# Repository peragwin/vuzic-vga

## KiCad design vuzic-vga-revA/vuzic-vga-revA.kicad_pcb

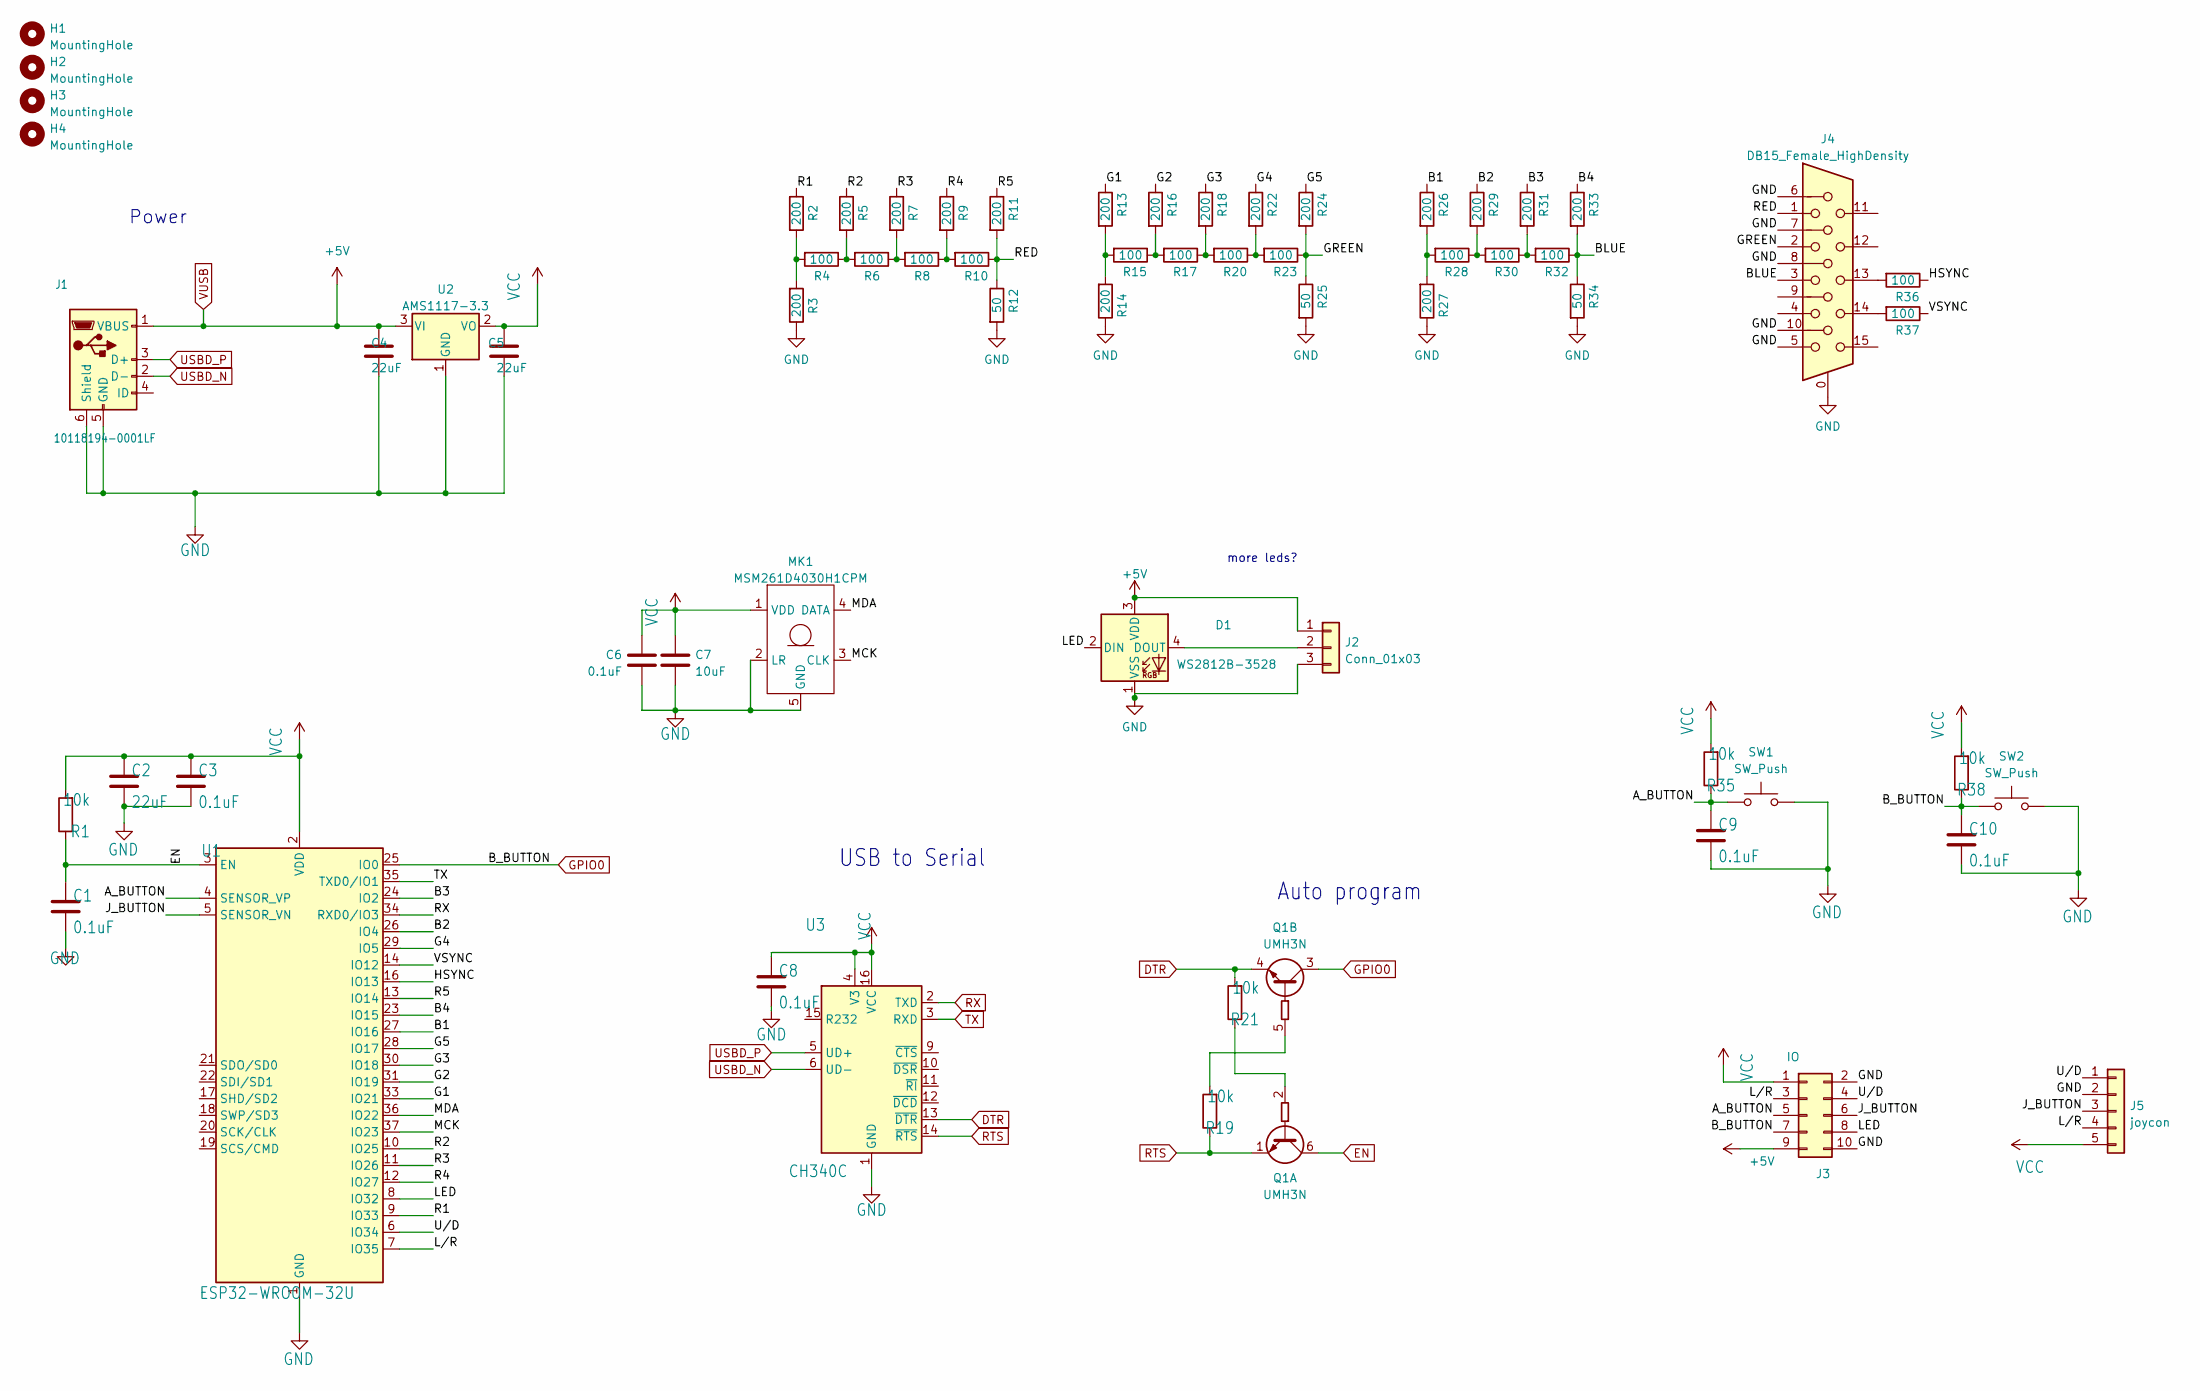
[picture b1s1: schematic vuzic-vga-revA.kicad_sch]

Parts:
C1, C6, C9, C10: 0.1uF; C_0402_1005Metric; LCSC C1525
C2, C4, C5: 22uF; C_1206_3216Metric; LCSC C5672
C3, C8: 0.1uF; C_0603_1608Metric; LCSC C1525
C7: 10uF; C_0603_1608Metric; LCSC C19702
D1: WS2812B-3528; LED_Kingbright_AAA3528ESGCT; LCSC C2890364
H1, H2, H3, H4: MountingHole; MountingHole_2.5mm
J1: 10118194-0001LF; USB_Micro-B_Amphenol_10118194_Horizontal; LCSC C132563
J2: Conn_01x03; PinHeader_1x03_P2.54mm_Vertical
J3: IO; PinHeader_2x05_P2.54mm_Vertical
J4: DB15_Female_HighDensity; DSUB-15-HD_Female_Horizontal_P2.29x1.98mm_EdgePinOffset3.03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; LCSC C138387
J5: joycon; LCSC C262654
MK1: MSM261D4030H1CPM; LCSC C966942
Q1: UMH3N; SOT-363_SC-70-6; LCSC C62892
R1, R19, R21, R35, R38: 10k; R_0402_1005Metric; LCSC C25744
R2, R3, R5, R7, R9, R11, R13, R14, R16, R18, R22, R24, R26, R27, R29, R31, R33: 200; R_0402_1005Metric; LCSC C25087
R4, R6, R8, R10, R15, R17, R20, R23, R28, R30, R32, R36, R37: 100; R_0402_1005Metric; LCSC C25076
R12, R25, R34: 50; R_0402_1005Metric; LCSC C25120
SW1, SW2: SW_Push; 1TS900A; LCSC C319411
U1: ESP32-WROOM-32U; ESP32-WROOM-32; LCSC C701341
U2: AMS1117-3.3; SOT-223-3_TabPin2; LCSC C6186
U3: CH340C; SOIC-16_3.9x9.9mm_P1.27mm; LCSC C84681

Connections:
+3V3: C2.1, C3.1, C5.1, C6.2, C7.1, C8.1, J3.1, J5.5, MK1.1 (VDD), R1.2, R35.2, R38.2, U1.2 (VDD), U2.2 (VO), U3.4 (V3), U3.16 (VCC)
/A_BUTTON: C9.1, J3.5, R35.1, SW1.1, U1.4 (SENSOR_VP)
/B1: R26.1, U1.27 (IO16)
/B2: R29.1, U1.26 (IO4)
/B3: R31.1, U1.24 (IO2)
/B4: R33.1, U1.23 (IO15)
/BLUE: J4.3, R32.1, R33.2, R34.1
/G1: R13.1, U1.33 (IO21)
/G2: R16.1, U1.31 (IO19)
/G3: R18.1, U1.30 (IO18)
/G4: R22.1, U1.29 (IO5)
/G5: R24.1, U1.28 (IO17)
/GREEN: J4.2, R23.1, R24.2, R25.1
/HSYNC: R36.1, U1.16 (IO13)
/J_BUTTON: J3.6, J5.3, U1.5 (SENSOR_VN)
/LED: D1.2 (DIN), J3.8, U1.8 (IO32)
/L/R: J3.3, J5.4, U1.7 (IO35)
/MCK: MK1.3 (CLK), U1.37 (IO23)
/MDA: MK1.4 (DATA), U1.36 (IO22)
/R1: R2.1, U1.9 (IO33)
/R2: R5.1, U1.10 (IO25)
/R3: R7.1, U1.11 (IO26)
/R4: R9.1, U1.12 (IO27)
/R5: R11.1, U1.13 (IO14)
/RED: J4.1, R10.1, R11.2, R12.1
/U/D: J3.4, J5.1, U1.6 (IO34)
/VSYNC: R37.1, U1.14 (IO12)
DTR: Q1.4 (E2), R21.2, U3.13 (~DTR)
EN: C1.1, Q1.6 (C1), R1.1, U1.3 (EN)
GND: C1.2, C2.2, C3.2, C4.2, C5.2, C6.1, C7.2, C8.2, C9.2, C10.2, D1.1 (VSS), J1.5 (GND), J1.6 (Shield), J2.3, J3.2, J3.10, J4.0, J4.5, J4.6, J4.7, J4.8, J4.10, J5.2, MK1.2 (LR), MK1.5 (GND), MK1.6 (GND), MK1.7 (GND), MK1.8 (GND), R3.1, R12.2, R14.1, R25.2, R27.1, R34.2, SW1.2, SW2.2, U1.1 (GND), U1.15 (GND), U1.38 (GND), U1.39 (GND), U2.1 (GND), U3.1 (GND)
GPIO0: C10.1, J3.7, Q1.3 (C2), R38.1, SW2.1, U1.25 (IO0)
unnamed: D1.4 (DOUT), J2.2
unnamed: J4.13, R36.2
unnamed: J4.14, R37.2
unnamed: Q1.2 (B1), R21.1
unnamed: Q1.5 (B2), R19.2
unnamed: R2.2, R3.2, R4.2
unnamed: R4.1, R5.2, R6.2
unnamed: R6.1, R7.2, R8.2
unnamed: R8.1, R9.2, R10.2
unnamed: R13.2, R14.2, R15.2
unnamed: R15.1, R16.2, R17.2
unnamed: R17.1, R18.2, R20.2
unnamed: R20.1, R22.2, R23.2
unnamed: R26.2, R27.2, R28.2
unnamed: R28.1, R29.2, R30.2
unnamed: R30.1, R31.2, R32.2
RTS: Q1.1 (E1), R19.1, U3.14 (~RTS)
RX: U1.34 (RXD0/IO3), U3.2 (TXD)
TX: U1.35 (TXD0/IO1), U3.3 (RXD)
USBD_N: J1.2 (D-), U3.6 (UD-)
USBD_P: J1.3 (D+), U3.5 (UD+)
VUSB: C4.1, D1.3 (VDD), J1.1 (VBUS), J2.1, J3.9, U2.3 (VI)

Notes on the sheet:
Power
USB to Serial
more leds?
Auto program

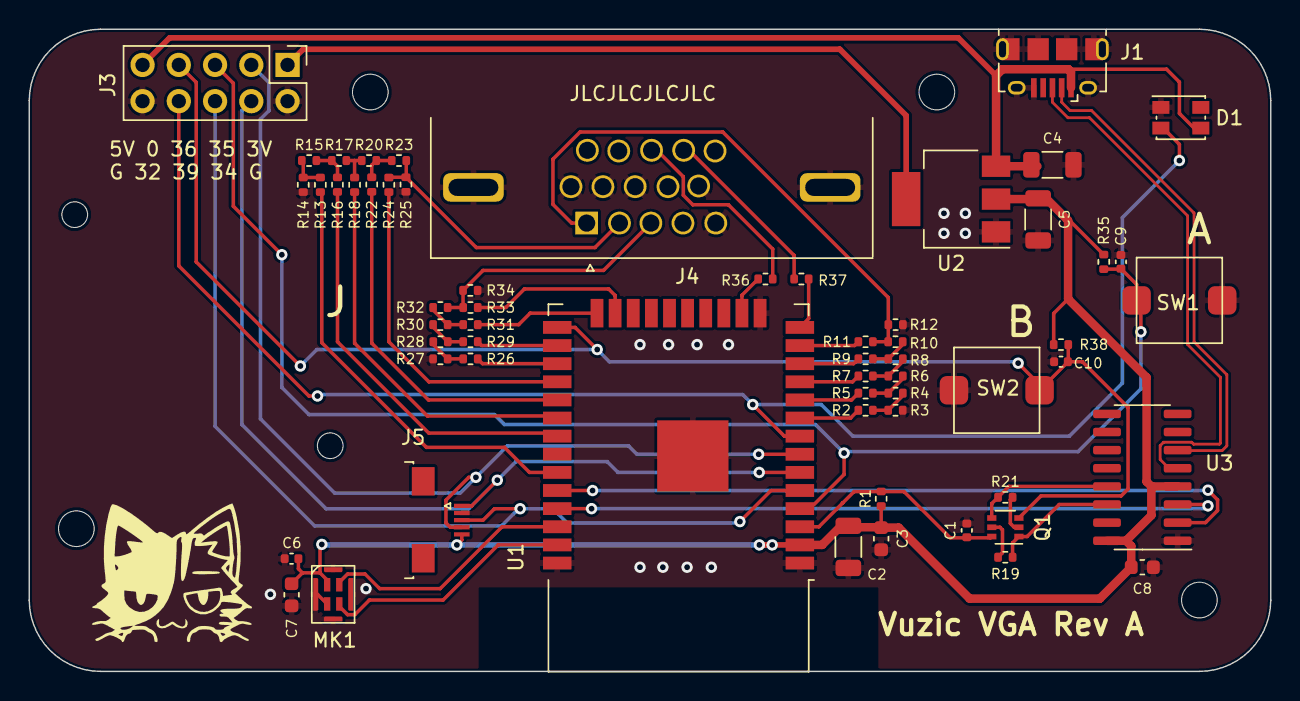
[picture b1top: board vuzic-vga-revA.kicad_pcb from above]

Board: 2 copper layers, 87.0 x 45.0 mm, 64 parts (0 on the bottom side), 52 nets.

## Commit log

2022-08-25 initial commit, vga revA
